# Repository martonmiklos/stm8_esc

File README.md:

# stm8_esc
Brushed motor controller built around STM8S003 and Allegro A3940/41 and N FETs

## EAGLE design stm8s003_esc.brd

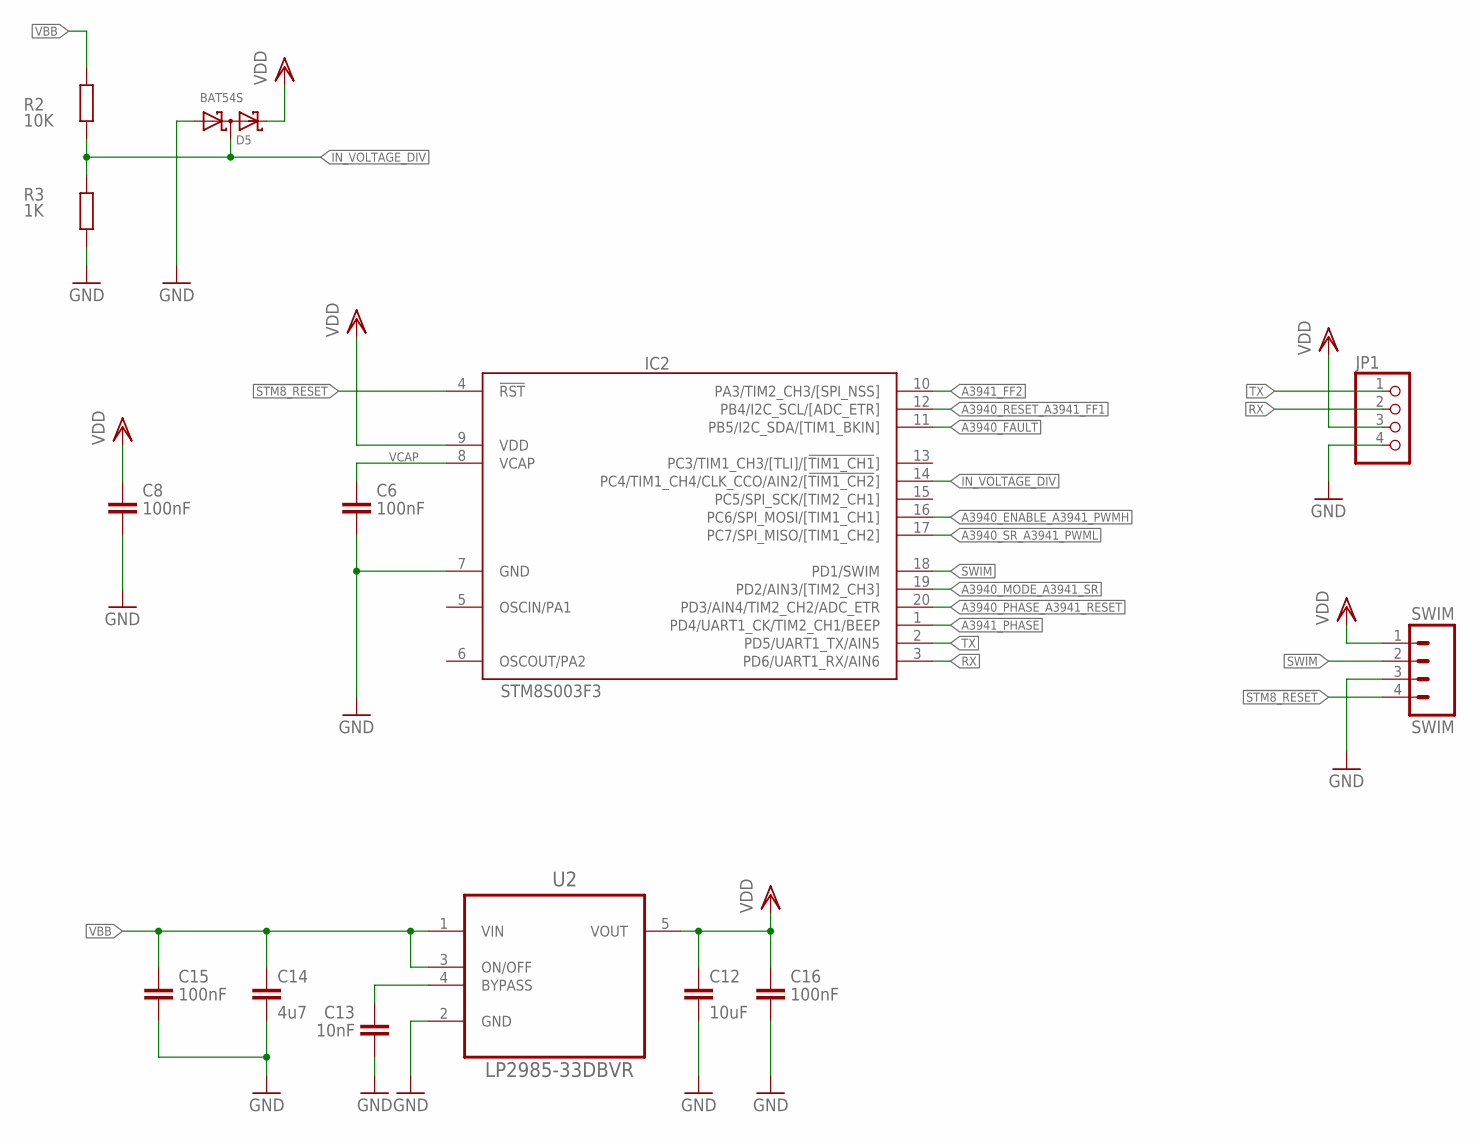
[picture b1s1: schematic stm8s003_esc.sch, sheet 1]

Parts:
C6, C8, C15: 100nF; C0603
C12: 10uF; C0805
C13: 10nF; C0603
C14: 4u7; C0805
C16: 100nF; C0603K
D5: BAT54S; SOT23
IC2: STM8S003F3; TSSOP20
JP1: PINHD-1X4; 1X04
R2: 10K; R0603
R3: 1K; R0603
SWIM: SWIM; 1X04-1.27MM
U2: LP2985-33DBVR; SOT95P284X119-5N

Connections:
!A3940_FAULT: IC2.11 (PB5/I2C_SDA/[TIM1_BKIN]); also elsewhere on the board
!STM8_RESET: IC2.4 (!RST), SWIM.4
A3940_ENABLE_A3941_PWMH: IC2.16 (PC6/SPI_MOSI/[TIM1_CH1]); also elsewhere on the board
A3940_MODE_A3941_SR: IC2.19 (PD2/AIN3/[TIM2_CH3]); also elsewhere on the board
A3940_PHASE_A3941_RESET: IC2.20 (PD3/AIN4/TIM2_CH2/ADC_ETR); also elsewhere on the board
A3940_RESET_A3941_FF1: IC2.12 (PB4/I2C_SCL/[ADC_ETR]); also elsewhere on the board
A3940_SR_A3941_PWML: IC2.17 (PC7/SPI_MISO/[TIM1_CH2]); also elsewhere on the board
A3941_FF2: IC2.10 (PA3/TIM2_CH3/[SPI_NSS]); also elsewhere on the board
A3941_PHASE: IC2.1 (PD4/UART1_CK/TIM2_CH1/BEEP); also elsewhere on the board
GND: C6.2, C8.2, C12.2, C13.2, C14.2, C15.2, C16.2, D5.1 (A1), IC2.7 (GND), JP1.4, R3.1, SWIM.3, U2.2 (GND); also elsewhere on the board
IN_VOLTAGE_DIV: D5.3 (C1A2), IC2.14 (PC4/TIM1_CH4/CLK_CCO/AIN2/[!TIM1_CH2!]), R2.1, R3.2
LP2985_BYPASS: C13.1, U2.4 (BYPASS)
RX: IC2.3 (PD6/UART1_RX/AIN6), JP1.2
SWIM: IC2.18 (PD1/SWIM), SWIM.2
TX: IC2.2 (PD5/UART1_TX/AIN5), JP1.1
VBB: C14.1, C15.1, R2.2, U2.1 (VIN), U2.3 (ON/OFF); also elsewhere on the board
VCAP: C6.1, IC2.8 (VCAP)
VDD: C8.1, C12.1, C16.1, D5.2 (C2), IC2.9 (VDD), JP1.3, SWIM.1, U2.5 (VOUT)

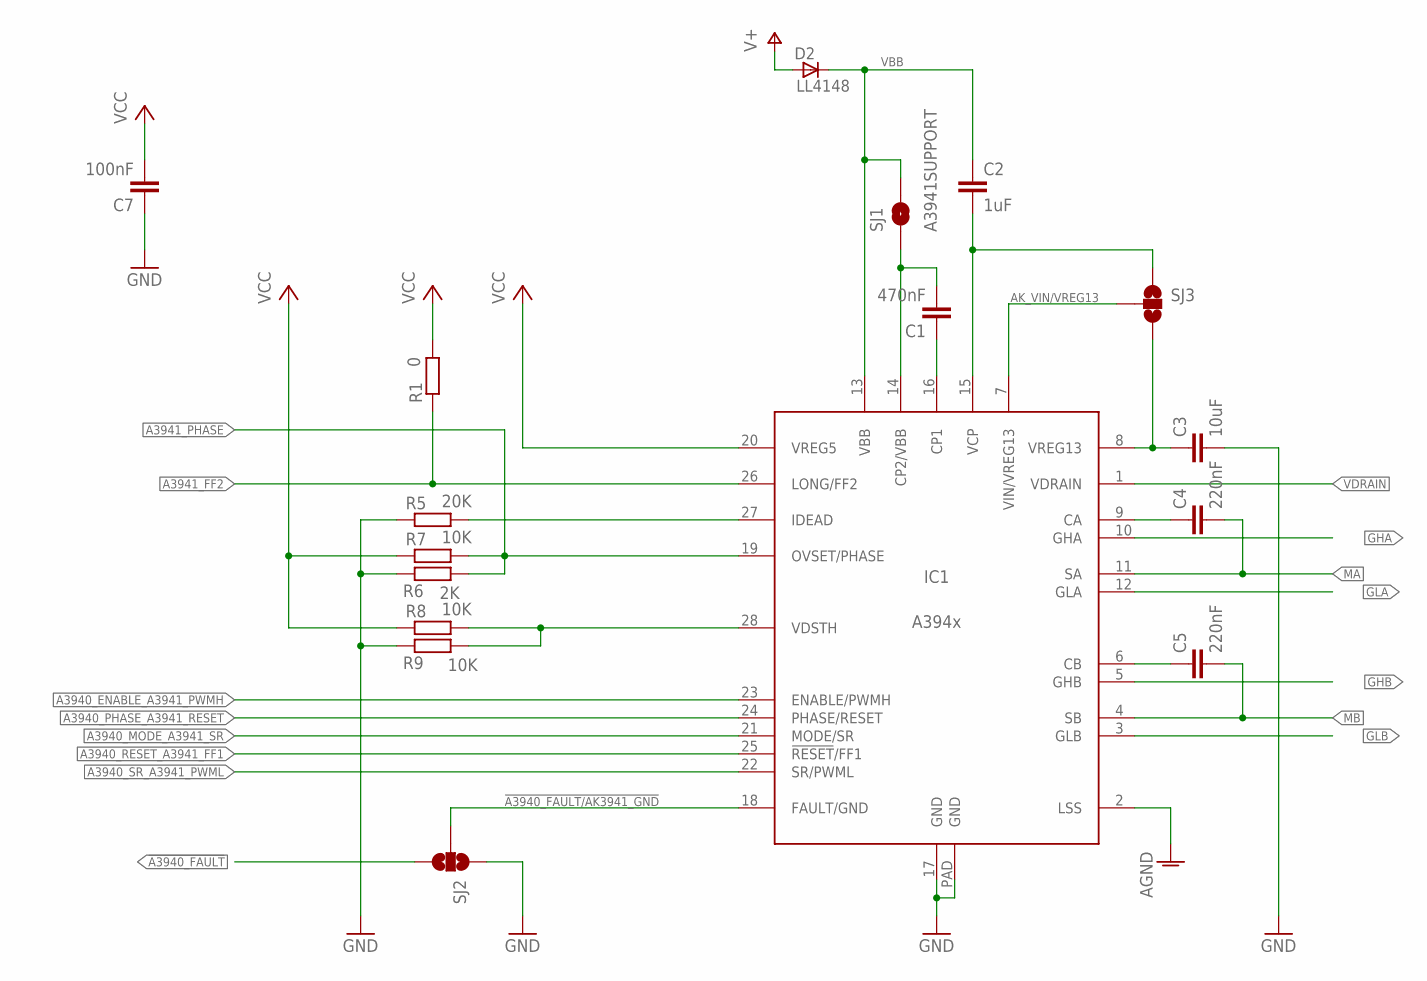
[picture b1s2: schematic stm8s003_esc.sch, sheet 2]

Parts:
C1: 470nF; C0603
C2: 1uF; C0603
C3: 10uF; C0603
C4, C5: 220nF; C0603
C7: 100nF; C0603
D2: LL4148; SOD80_DO213AA_MINIMELF
IC1: A394x; TSSOP28-PAD
R1: 0; R0603
R5: 20K; R0603
R6: 2K; R0603
R7, R8, R9: 10K; R0603
SJ1: A3941SUPPORT; SJ_2S-NO
SJ2, SJ3: SOLDERJUMPER_2WAYPASTE2&3; SJ_3_PASTE2&3

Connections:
!A3940_FAULT: SJ2.3; also elsewhere on the board
!A3940_FAULT/AK3941_GND: IC1.18 (FAULT/GND), SJ2.2
A3940_ENABLE_A3941_PWMH: IC1.23 (ENABLE/PWMH); also elsewhere on the board
A3940_MODE_A3941_SR: IC1.21 (MODE/SR); also elsewhere on the board
A3940_PHASE_A3941_RESET: IC1.24 (PHASE/RESET); also elsewhere on the board
A3940_RESET_A3941_FF1: IC1.25 (!RESET!/FF1); also elsewhere on the board
A3940_SR_A3941_PWML: IC1.22 (SR/PWML); also elsewhere on the board
A3941_FF2: IC1.26 (LONG/FF2), R1.1; also elsewhere on the board
A3941_PHASE: IC1.19 (OVSET/PHASE), R6.1, R7.2; also elsewhere on the board
AGND: IC1.2 (LSS); also elsewhere on the board
AK_CA: C4.1, IC1.9 (CA)
AK_CB: C5.1, IC1.6 (CB)
AK_VDSTH: IC1.28 (VDSTH), R8.2, R9.1
AK_VIN/VREG13: IC1.7 (VIN/VREG13), SJ3.2
AK_VREG13: C3.1, IC1.8 (VREG13), SJ3.3
CP1: C1.1, IC1.16 (CP1)
CP2: C1.2, IC1.14 (CP2/VBB), SJ1.1
GHA: IC1.10 (GHA); also elsewhere on the board
GHB: IC1.5 (GHB); also elsewhere on the board
GLA: IC1.12 (GLA); also elsewhere on the board
GLB: IC1.3 (GLB); also elsewhere on the board
GND: C3.2, C7.1, IC1.17 (GND), IC1.PAD (GND), R5.1, R6.2, R9.2, SJ2.1; also elsewhere on the board
IDEAD: IC1.27 (IDEAD), R5.2
MA: C4.2, IC1.11 (SA)
MB: C5.2, IC1.4 (SB)
V+: D2.A; also elsewhere on the board
VBB: C2.1, D2.C, IC1.13 (VBB), SJ1.2; also elsewhere on the board
VCC: C7.2, IC1.20 (VREG5), R1.2, R7.1, R8.1
VCP: C2.2, IC1.15 (VCP), SJ3.1
VDRAIN: IC1.1 (VDRAIN); also elsewhere on the board

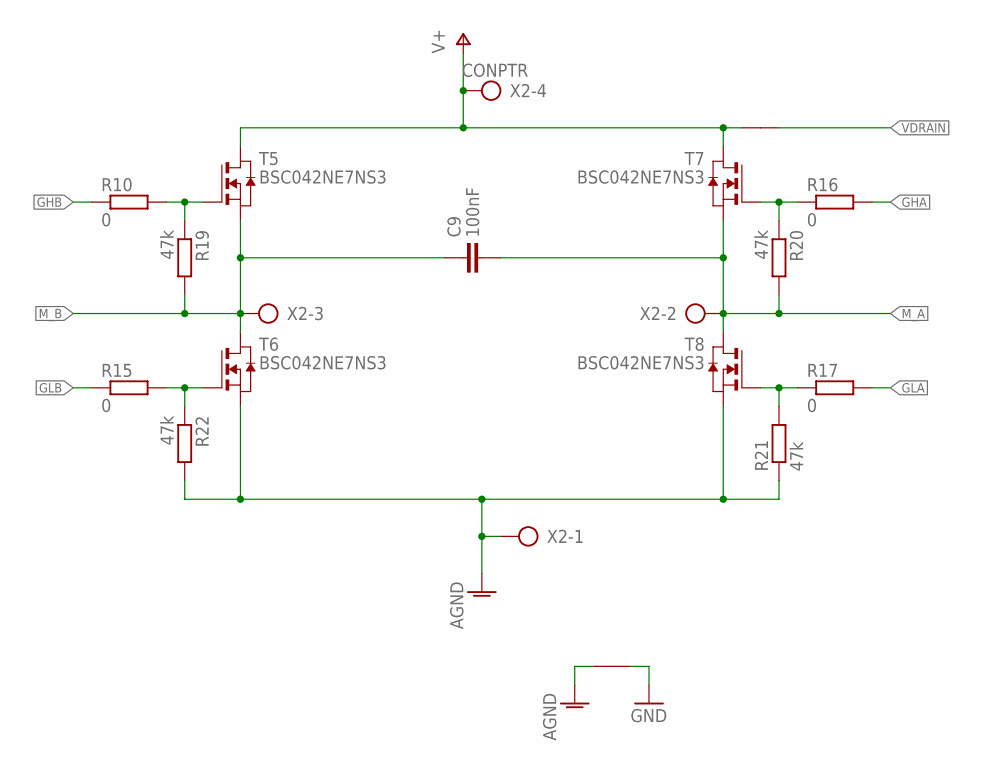
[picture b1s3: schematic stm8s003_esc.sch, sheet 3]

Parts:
C9: 100nF; C0603
GND_JUNCTION: AGND_DGND_JUNCTION
R10, R15, R16, R17: 0; R0603
R19, R20, R21, R22: 47k; R0603
T5, T6, T7, T8: BSC042NE7NS3; PG-TDSON-8
V+_JUNCTION: AGND_DGND_JUNCTION
X2: CONPTR; AK300/4

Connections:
AGND: GND_JUNCTION.AGND, R21.1, R22.2, T6.1 (S), T6.2 (S), T6.3 (S), T8.1 (S), T8.2 (S), T8.3 (S), X2.1; also elsewhere on the board
GHA: R16.2; also elsewhere on the board
GHA_R: R16.1, R20.1, T7.4 (G)
GHB: R10.1; also elsewhere on the board
GHB_R: R10.2, R19.1, T5.4 (G)
GLA: R17.2; also elsewhere on the board
GLA_R: R17.1, R21.2, T8.4 (G)
GLB: R15.1; also elsewhere on the board
GLB_R: R15.2, R22.1, T6.4 (G)
GND: GND_JUNCTION.DGND; also elsewhere on the board
M_A: C9.2, R20.2, T7.1 (S), T7.2 (S), T7.3 (S), T8.5 (D), T8.6 (D), T8.7 (D), T8.8 (D), T8.D, X2.2
M_B: C9.1, R19.2, T5.1 (S), T5.2 (S), T5.3 (S), T6.5 (D), T6.6 (D), T6.7 (D), T6.8 (D), T6.D, X2.3
V+: T5.5 (D), T5.6 (D), T5.7 (D), T5.8 (D), T5.D, T7.5 (D), T7.6 (D), T7.7 (D), T7.8 (D), T7.D, V+_JUNCTION.AGND, X2.4; also elsewhere on the board
VDRAIN: V+_JUNCTION.DGND; also elsewhere on the board

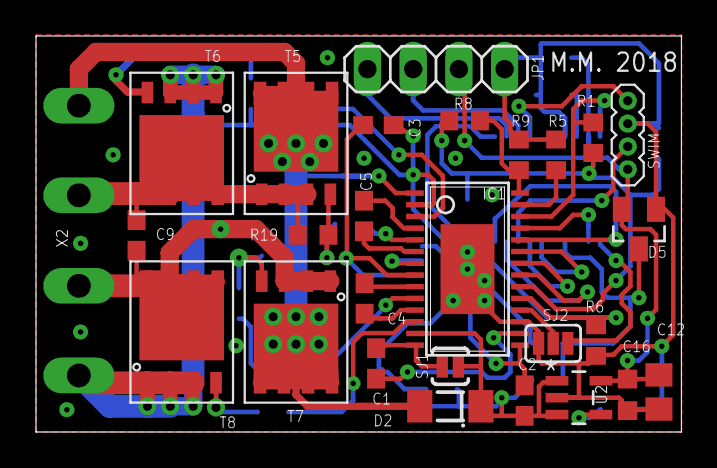
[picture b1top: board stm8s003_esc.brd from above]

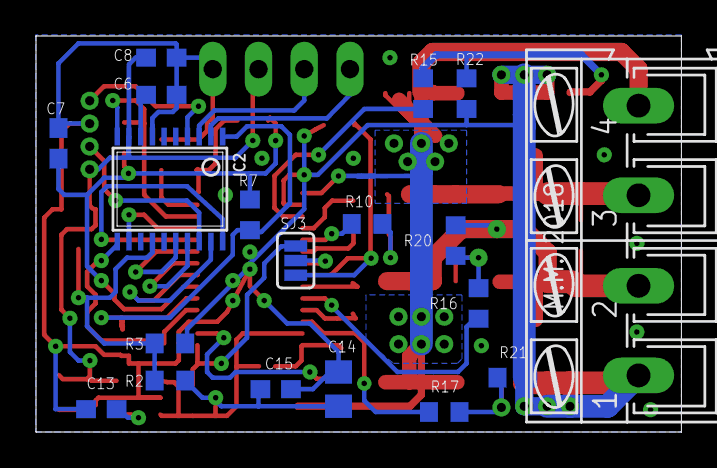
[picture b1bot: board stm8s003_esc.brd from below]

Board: 2 copper layers, 35.9 x 22.0 mm, 47 parts (21 on the bottom side), 44 nets.

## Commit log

2018-09-07 Daily save
2018-09-07 Add SCH & IOC file

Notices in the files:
parts and their libraries:
SparkFun: Licensing: CC v3.0 Share-Alike You are welcome to use this library for commercial purposes.
